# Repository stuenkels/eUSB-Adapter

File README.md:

# eUSB to USB-A Adapter
Adapts embedded USB drives to USB-A. Created to backup Juniper Switch drives but can work with any 5v eUSB drive. Uses eUSB legacay connector non-stacking.

## BOM
| Identifier | Description                  | Part Number           |
|------------|------------------------------|-----------------------|
| J1         | eUSB Connector               | 2*5 2.54mm Pin header |
| J2         | USB-A Connector              | TE_1-1734028-1        |
| D1         | Activity LED                 | 0805 SMD LED          |
| D2         | Power LED                    | 0805 SMD LED          |
| R1         | Activity LED Current Limiter | 1KΩ 0603 SMD Resistor |
| R2         | Power LED Current Limiter    | 1KΩ 0603 SMD Resistor |

## 3d Render Front

## 3d Render Back

## 3d Top

## With eUSB Drive Attached

## Plugged into Computer

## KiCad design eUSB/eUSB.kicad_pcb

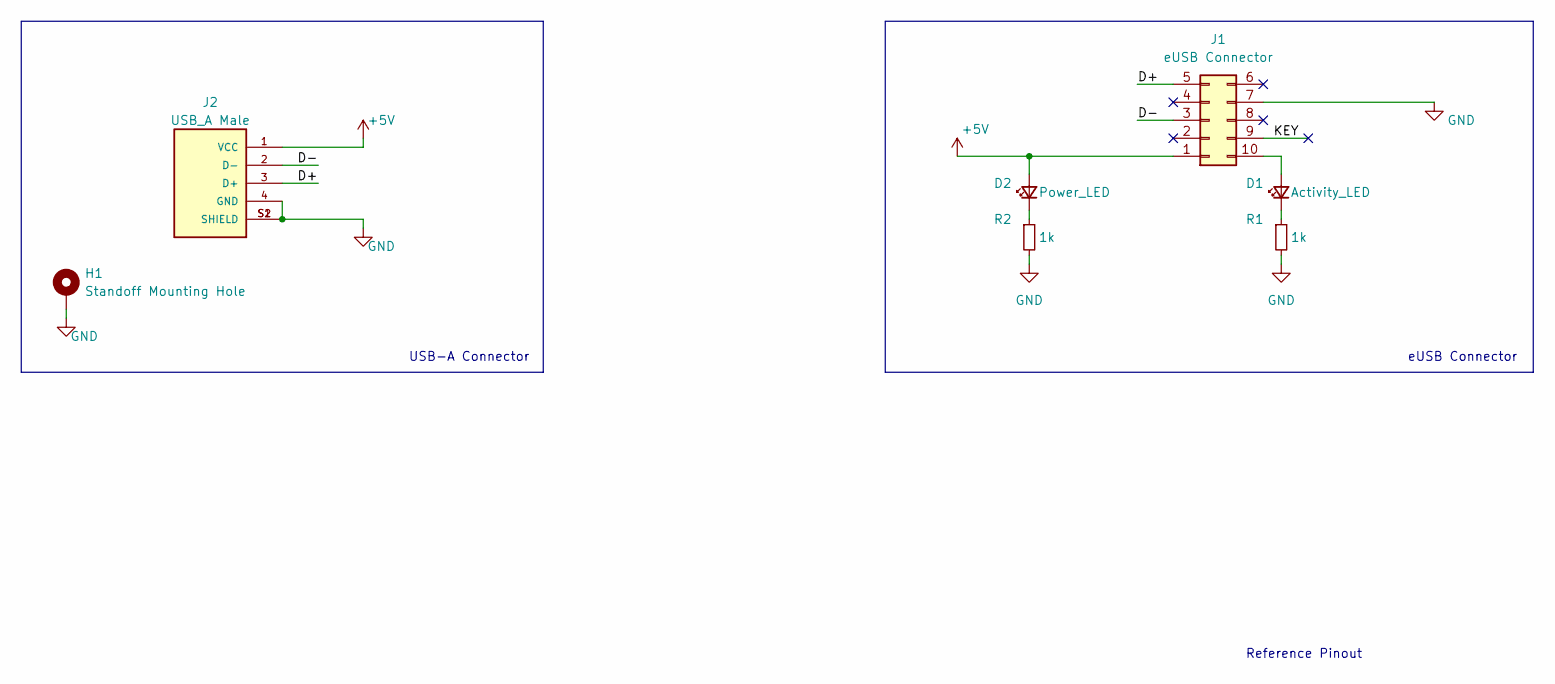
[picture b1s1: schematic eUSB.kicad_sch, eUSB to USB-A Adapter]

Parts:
D1: Activity_LED; LED_0805_2012Metric
D2: Power_LED; LED_0805_2012Metric
H1: Standoff Mounting Hole; MountingHole_3.2mm_M3_ISO7380_Pad
J1: eUSB Connector; PinHeader_2x05_P2.54mm_Vertical
J2: USB_A Male; TE_1-1734028-1; PARTREV C
R1, R2: 1k; R_0603_1608Metric

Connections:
+5V: D2.2 (A), J1.1, J2.1 (VCC)
/D+: J1.5, J2.3 (D+)
/D-: J1.3, J2.2 (D-)
/KEY: J1.9
GND: H1.1, J1.7, J2.4 (GND), J2.S1 (SHIELD), J2.S2 (SHIELD), R1.2, R2.2
unnamed: D1.1 (K), R1.1
unnamed: D1.2 (A), J1.10
unnamed: D2.1 (K), R2.1

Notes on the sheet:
USB-A Connector
eUSB Connector
Reference Pinout

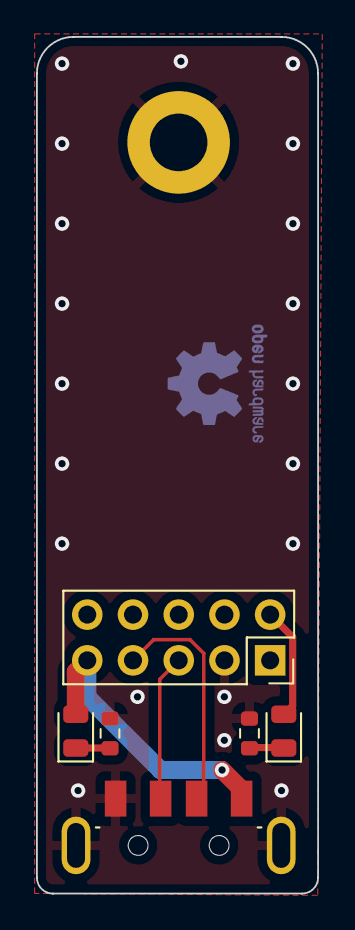
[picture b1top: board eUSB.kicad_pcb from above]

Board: 2 copper layers, 15.6 x 47.6 mm, 7 parts (0 on the bottom side), 7 nets.

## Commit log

2025-01-09 update to relative paths
2025-01-09 updated silkscrean
2025-01-10 Edited readme
2025-01-10 update readme add BOM
2025-01-10 remove uneaded html file
2025-01-10 why this untracked?
2025-02-27 Add pretty pictures
2025-02-27 Create Readme and add link to onshape
2025-02-27 Upload STL files
2025-02-27 Typo
